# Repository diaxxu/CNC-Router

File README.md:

# CNC-Router

This is my homemade modular CNC machine, built from simple available parts. I designed everything in Fusion 360, researched every component, and chose them carefully. It’s not perfect, but it’s beautiful, and I genuinely enjoyed building it.

## Why I Made This

To get more hands on experience ? this is a very cool project. A CNC that can carve wood and maybe on a good day cut aluminum, isn't that great ?

## 3D Model 

### Front View

### Side View

### Full Assembly

## Schematics and PCB Layout
**made it in Kicad** 

(i re-routed this 5 or 6 times 😭) </br>

im really bad at soldering :c </br>
### Schematic ( wire diagram ) 

## Firmware Installation 
1- assemble your driver board ( put the driver in plane ) Insert it into the Arduino Uno header <br/>
2- connect the arduino uno your pc<br/> 
3- download grbl.zip from the github <br/>
4- upload the code <br/>
5- install Universal Gcode sender <br/>
6- learn CAM software or use Easel <br/>
7- enjoy the results <br/>

## BOM (Bill of Materials)

Here is the secret sauce!!

| Item                                     | Quantity | Unit |   link|
| ---------------------------------------- | -------- | ---- |      ---------------------------------------- |
| T8 Lead Screw 2mm lead 500 mm (with nut) | 1        | pcs  |          https://www.aliexpress.com/item/1005007457419235.html?spm=a2g0o.productlist.main.1.13e96abcm3Qxf8&algo_pvid=abe9b885-1ea4-4bde-81db-ef474f83f248&pdp_ext_f=%7B%22order%22%3A%221334%22%2C%22eval%22%3A%221%22%2C%22fromPage%22%3A%22search%22%7D&utparam-url=scene%3Asearch%7Cquery_from%3A%7Cx_object_id%3A1005007457419235%7C_p_origin_prod%3A                                      |
| T8 screw round                           | 10       | pcs  |  https://www.aliexpress.com/item/1005007438925484.html?spm=a2g0o.productlist.main.1.663d47d6Xk5GhJ&algo_pvid=a073f148-42f6-4d7e-ae10-4d699659c8fb&pdp_ext_f=%7B%22order%22%3A%22195%22%2C%22eval%22%3A%221%22%2C%22fromPage%22%3A%22search%22%7D&utparam-url=scene%3Asearch%7Cquery_from%3A%7Cx_object_id%3A1005007438925484%7C_p_origin_prod%3A                                         |
| LM6UU linear bearing                     | 4        | pcs  |  https://www.aliexpress.com/item/1005007791097936.html?spm=a2g0o.productlist.main.1.3edb5583NcR1Fg&algo_pvid=f794e0da-0bcf-4ead-a3f3-0a383e8e83e8&pdp_ext_f=%7B%22order%22%3A%221004%22%2C%22eval%22%3A%221%22%2C%22orig_sl_item_id%22%3A%221005007791097936%22%2C%22orig_item_id%22%3A%221005006822845504%22%2C%22fromPage%22%3A%22search%22%7D&utparam-url=scene%3Asearch%7Cquery_from%3A%7Cx_object_id%3A1005007791097936%7C_p_origin_prod%3A1005006822845504                                         |
| NEMA17 stepper motor                     | 3        | pcs  |       https://www.aliexpress.com/item/1005003874936862.html?spm=a2g0o.productlist.main.1.3135692aSn653o&algo_pvid=01a18a8a-84a6-4b73-875e-59fb750efacf&pdp_ext_f=%7B%22order%22%3A%222333%22%2C%22eval%22%3A%221%22%2C%22fromPage%22%3A%22search%22%7D&utparam-url=scene%3Asearch%7Cquery_from%3A%7Cx_object_id%3A1005003874936862%7C_p_origin_prod%3A                                     |
| M5 T-nut for 2020 extrusion              | 100      | pcs  |     https://www.aliexpress.com/item/1005007805744044.html?spm=a2g0o.productlist.main.1.21166df09vtnEI&algo_pvid=d509197c-5494-4b8d-bd75-dd62f6435446&pdp_ext_f=%7B%22order%22%3A%222654%22%2C%22spu_best_type%22%3A%22price%22%2C%22eval%22%3A%221%22%2C%22orig_sl_item_id%22%3A%221005007805744044%22%2C%22orig_item_id%22%3A%221005007342221792%22%2C%22fromPage%22%3A%22search%22%7D&utparam-url=scene%3Asearch%7Cquery_from%3A%7Cx_object_id%3A1005007805744044%7C_p_origin_prod%3A1005007342221792                                          |
| Shaft decoupler                          | 5        | pcs  |     https://www.aliexpress.com/item/1005006031199563.html?spm=a2g0o.productlist.main.9.44996081ngFjnD&algo_pvid=ea42cc85-9204-4080-b783-f4bf5ca40faf&pdp_ext_f=%7B%22order%22%3A%221177%22%2C%22eval%22%3A%221%22%2C%22fromPage%22%3A%22search%22%7D&utparam-url=scene%3Asearch%7Cquery_from%3A%7Cx_object_id%3A1005006031199563%7C_p_origin_prod%3A             |
| Limit switch (mechanical)                | 5        | pcs  |           https://www.aliexpress.com/item/1005010111182286.html?spm=a2g0o.productlist.main.1.3abbDG8vDG8vWA&algo_pvid=5933562e-580b-41ea-b598-2eb9fccb11d4&pdp_ext_f=%7B%22order%22%3A%223%22%2C%22eval%22%3A%221%22%2C%22fromPage%22%3A%22search%22%7D&utparam-url=scene%3Asearch%7Cquery_from%3A%7Cx_object_id%3A1005010111182286%7C_p_origin_prod%3A        |           
| Smooth shaft ~8mm x 500mm                | 2        | pcs  |               https://www.aliexpress.com/item/1005006104915821.html?spm=a2g0o.productlist.main.1.799f489bStEF77&algo_pvid=020c6d09-a195-4892-a017-91578b69bc51&pdp_ext_f=%7B%22order%22%3A%22162%22%2C%22eval%22%3A%221%22%2C%22fromPage%22%3A%22search%22%7D&utparam-url=scene%3Asearch%7Cquery_from%3A%7Cx_object_id%3A1005006104915821%7C_p_origin_prod%3A      |
| 2020 T-slot extrusion 300mm              | 4        | pcs  |                https://www.aliexpress.com/item/1005002652962344.html?spm=a2g0o.productlist.main.2.2e3437d7dGcIn6&algo_pvid=0aca7721-a8b6-4cf1-8678-ae9d48901605&pdp_ext_f=%7B%22order%22%3A%22609%22%2C%22eval%22%3A%221%22%2C%22fromPage%22%3A%22search%22%7D&utparam-url=scene%3Asearch%7Cquery_from%3A%7Cx_object_id%3A1005002652962344%7C_p_origin_prod%3A       |
| Emergency stop button                    | 1        | pcs  |            https://www.aliexpress.com/item/4000144892605.html?spm=a2g0o.productlist.main.6.33636377MQJT7H&algo_pvid=5d4f84aa-a965-43b3-a225-a805972d57df&pdp_ext_f=%7B%22order%22%3A%22186%22%2C%22eval%22%3A%221%22%2C%22fromPage%22%3A%22search%22%7D&utparam-url=scene%3Asearch%7Cquery_from%3A%7Cx_object_id%3A4000144892605%7C_p_origin_prod%3A         |
| Spindle                                  | 1        | pcs  |              https://www.aliexpress.com/item/1005006435477384.html?spm=a2g0o.productlist.main.9.2c031bb1jvPHgq&algo_pvid=c00a937d-d03c-4e7d-8a0f-f253cf034e65&pdp_ext_f=%7B%22order%22%3A%22110%22%2C%22eval%22%3A%221%22%2C%22fromPage%22%3A%22search%22%7D&utparam-url=scene%3Asearch%7Cquery_from%3A%7Cx_object_id%3A1005006435477384%7C_p_origin_prod%3A          |
| 4 flute HRC65 end mill                   | 4        | pcs  |                 https://www.aliexpress.com/item/1005006112116580.html?spm=a2g0o.productlist.main.1.28a91ef71Q6Qi6&algo_pvid=7d58d743-c4fb-4f96-9785-83c5d507e746&pdp_ext_f=%7B%22order%22%3A%223827%22%2C%22eval%22%3A%221%22%2C%22fromPage%22%3A%22search%22%7D&utparam-url=scene%3Asearch%7Cquery_from%3A%7Cx_object_id%3A1005006112116580%7C_p_origin_prod%3A          |
| Esp-32 wroom32                           |  1       | pcs  |          https://www.aliexpress.com/item/1005007117977294.html?spm=a2g0o.productlist.main.4.378a251bueFwB6&aem_p4p_detail=202512120410314090179256483500000207938&algo_pvid=bdf25448-9590-4bd6-97b4-afa84b8659dc&pdp_ext_f=%7B%22order%22%3A%22475%22%2C%22eval%22%3A%221%22%2C%22fromPage%22%3A%22search%22%7D&utparam-url=scene%3Asearch%7Cquery_from%3A%7Cx_object_id%3A1005007117977294%7C_p_origin_prod%3A&search_p4p_id=202512120410314090179256483500000207938_1              |
| Capacitor 100uF                 | 40        | pcs   |                           https://www.aliexpress.com/item/1005007792451411.html?spm=a2g0o.productlist.main.2.2ba17329lFhLJc&algo_pvid=0bc21b08-f505-443c-9b1e-3c51c8b5715e&pdp_ext_f=%7B%22order%22%3A%224566%22%2C%22eval%22%3A%221%22%2C%22orig_sl_item_id%22%3A%221005007792451411%22%2C%22orig_item_id%22%3A%221005009331775121%22%2C%22fromPage%22%3A%22search%22%7D&utparam-url=scene%3Asearch%7Cquery_from%3A%7Cx_object_id%3A1005007792451411%7C_p_origin_prod%3A1005009331775121            |
| DRV8825              |5      | pcs   |            https://www.aliexpress.com/item/1005006199405206.html?spm=a2g0o.productlist.main.1.2ac830b537vAT5&algo_pvid=251ba9a3-c089-40c5-95d6-3f10fed98294&pdp_ext_f=%7B%22order%22%3A%221189%22%2C%22eval%22%3A%221%22%2C%22fromPage%22%3A%22search%22%7D&utparam-url=scene%3Asearch%7Cquery_from%3A%7Cx_object_id%3A1005006199405206%7C_p_origin_prod%3A           |
| irlz44n            |10     | pcs   |                     https://www.aliexpress.com/item/32895956089.html?spm=a2g0o.productlist.main.3.585c7f81SrpjDa&algo_pvid=217b9e85-fb72-4510-a7c3-e3ecc2203bdb&pdp_ext_f=%7B%22order%22%3A%22330%22%2C%22eval%22%3A%221%22%2C%22fromPage%22%3A%22search%22%7D&utparam-url=scene%3Asearch%7Cquery_from%3A%7Cx_object_id%3A32895956089%7C_p_origin_prod%3A              |
| 1N5819          |50     | pcs   |                       https://www.aliexpress.com/item/1005001552094086.html?algo_pvid=6702d0a0-3a5b-4a89-a69c-304c6e60e806&pdp_ext_f=%7B%22order%22%3A%223075%22%2C%22eval%22%3A%221%22%2C%22fromPage%22%3A%22search%22%7D&utparam-url=scene%3Asearch%7Cquery_from%3A%7Cx_object_id%3A1005001552094086%7C_p_origin_prod%3A       |
| Screw terminal         |10     | pcs   |                     https://www.aliexpress.com/item/1005001677869988.html?spm=a2g0o.productlist.main.4.22797cf5vgQYyY&aem_p4p_detail=20251212041208392676109231120000190813&algo_pvid=ef3df8c8-928a-4232-a6dc-efeceac0b4f4&pdp_ext_f=%7B%22order%22%3A%222679%22%2C%22eval%22%3A%221%22%2C%22fromPage%22%3A%22search%22%7D&utparam-url=scene%3Asearch%7Cquery_from%3A%7Cx_object_id%3A1005001677869988%7C_p_origin_prod%3A&search_p4p_id=20251212041208392676109231120000190813_1             |
| Pin headers 1*40pin        |10     | pcs   |                     https://www.aliexpress.com/item/32980998451.html?spm=a2g0o.productlist.main.4.6ff54f9dFpS61i&aem_p4p_detail=202512120412263191470227330580000181648&algo_pvid=725f76e7-70a3-44bd-9da3-b267a7eabeb5&pdp_ext_f=%7B%22order%22%3A%22149%22%2C%22eval%22%3A%221%22%2C%22fromPage%22%3A%22search%22%7D&utparam-url=scene%3Asearch%7Cquery_from%3A%7Cx_object_id%3A32980998451%7C_p_origin_prod%3A&search_p4p_id=202512120412263191470227330580000181648_1               |
| PSU 24V 16A       |1    | pcs   |                    https://www.aliexpress.com/item/1005003962776196.html?spm=a2g0o.productlist.main.1.14347ac40PBlA3&algo_pvid=1247abea-e56f-4125-8b5c-04adc4c23b2b&pdp_ext_f=%7B%22order%22%3A%2211%22%2C%22eval%22%3A%221%22%2C%22fromPage%22%3A%22search%22%7D&utparam-url=scene%3Asearch%7Cquery_from%3A%7Cx_object_id%3A1005003962776196%7C_p_origin_prod%3A|
| pcb cost | 5 | pcs |  https://www.allpcb.com/cart?protype=2&upfileid=797791 |
| 3d printing cost | 456 | grams |  fusion estimation |
### Total 
- in Mad : 3.512 </br>
- in Dollar : 384.72

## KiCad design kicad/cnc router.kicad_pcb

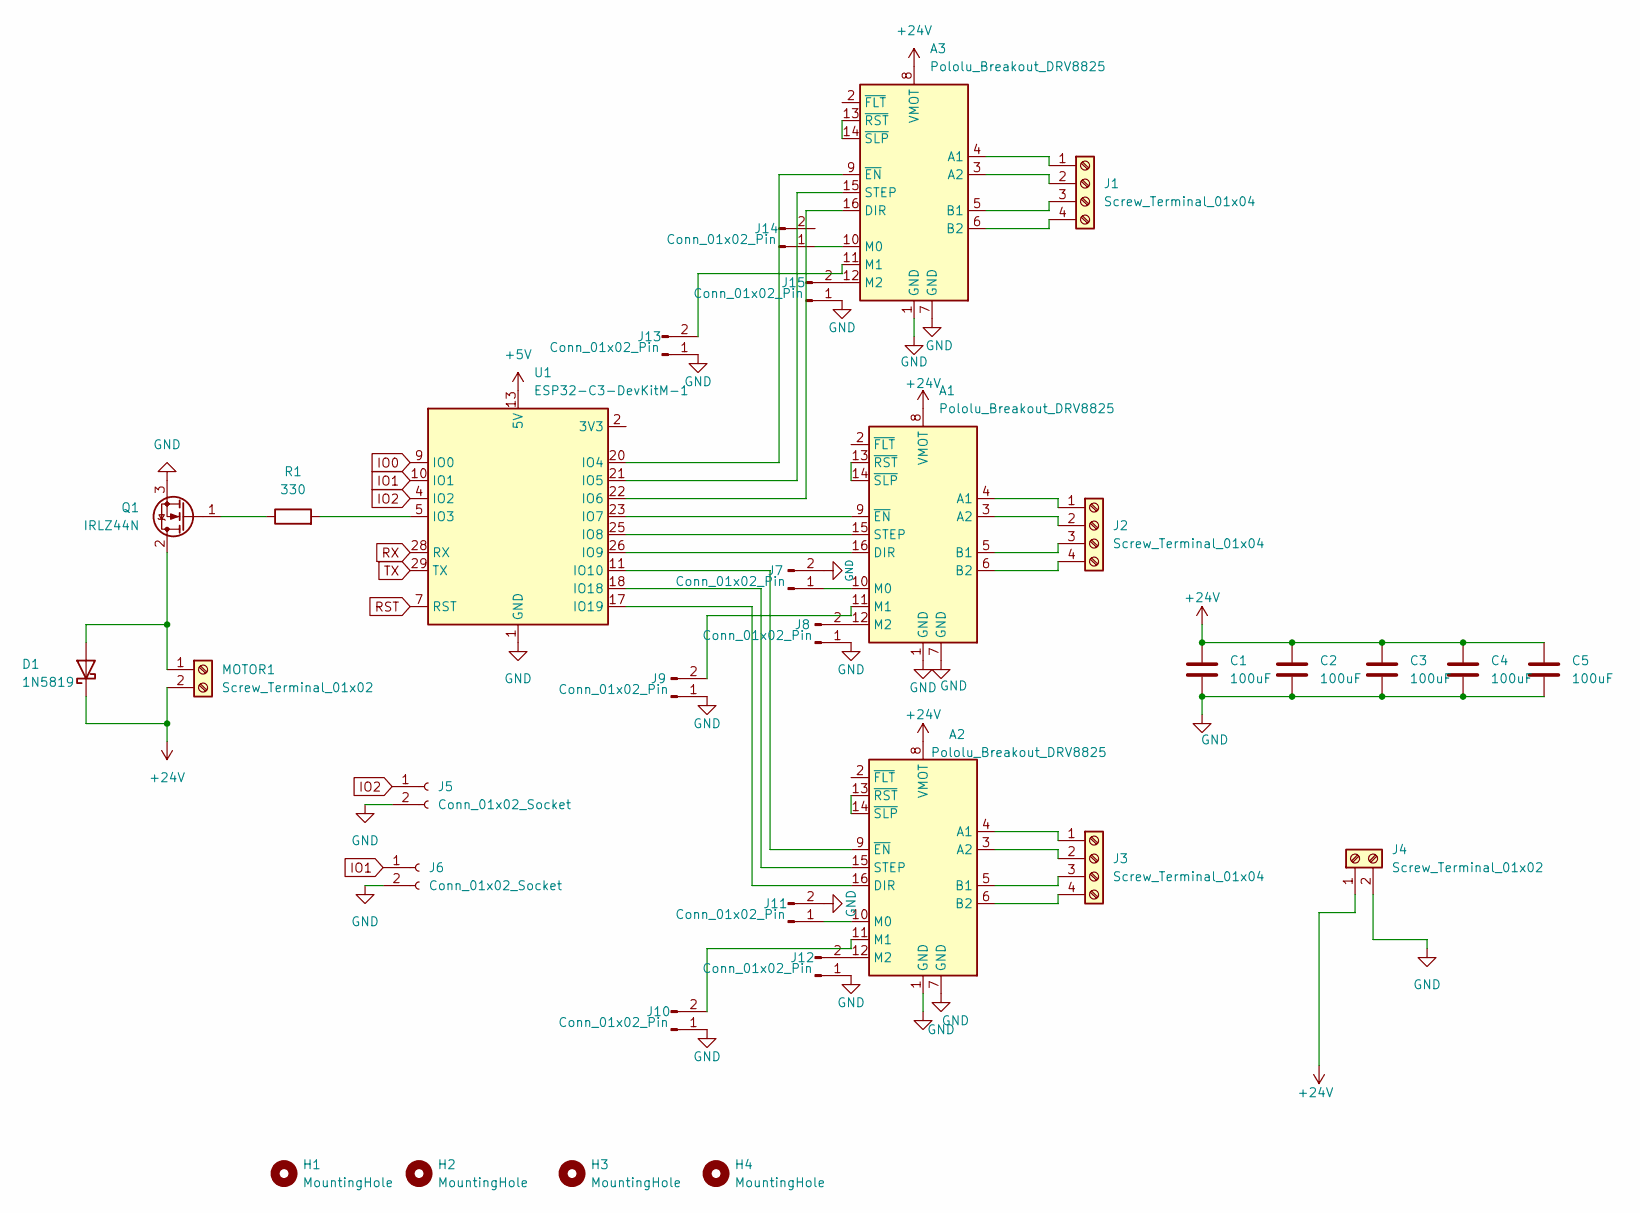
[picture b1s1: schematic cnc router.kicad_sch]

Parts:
A1, A2, A3: Pololu_Breakout_DRV8825; Pololu_Breakout-16_15.2x20.3mm
C1, C2, C3, C4, C5: 100uF; R_Axial_DIN0516_L15.5mm_D5.0mm_P30.48mm_Horizontal
D1: 1N5819; D_DO-41_SOD81_P10.16mm_Horizontal
H1, H2, H3, H4: MountingHole; MountingHole_2.1mm
J1, J2, J3: Screw_Terminal_01x04; TerminalBlock_Phoenix_MKDS-1,5-4-5.08_1x04_P5.08mm_Horizont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
J4: Screw_Terminal_01x02; TerminalBlock_Phoenix_MKDS-1,5-2_1x02_P5.00mm_Horizontal
J5, J6: Conn_01x02_Socket; PinSocket_1x02_P2.00mm_Vertical
J7, J8, J9, J10, J11, J12, J13, J14, J15: Conn_01x02_Pin; PinHeader_1x02_P2.54mm_Vertical
MOTOR1: Screw_Terminal_01x02; TerminalBlock_Phoenix_MKDS-1,5-2_1x02_P5.00mm_Horizontal
Q1: IRLZ44N; TO-220-3_Vertical
R1: 330; R_Axial_Power_L20.0mm_W6.4mm_P22.40mm
U1: ESP32-C3-DevKitM-1

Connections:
+5V: U1.13 (5V), U1.14 (5V)
+24V: A1.8 (VMOT), A2.8 (VMOT), A3.8 (VMOT), C1.1, C2.1, C3.1, C4.1, C5.1, D1.1 (K), J4.1, MOTOR1.2
GND: A1.1 (GND), A1.7 (GND), A2.1 (GND), A2.7 (GND), A3.1 (GND), A3.7 (GND), C1.2, C2.2, C3.2, C4.2, C5.2, J4.2, J5.2, J6.2, J7.2, J8.1, J9.1, J10.1, J11.2, J12.1, J13.1, J15.1, Q1.3 (S), U1.1 (GND), U1.6 (GND), U1.8 (GND), U1.12 (GND), U1.15 (GND), U1.16 (GND), U1.19 (GND), U1.24 (GND), U1.27 (GND), U1.30 (GND)
IO0: U1.9 (IO0)
IO1: J6.1, U1.10 (IO1)
IO2: J5.1, U1.4 (IO2)
unnamed: A1.4 (A1), J2.1
unnamed: A1.3 (A2), J2.2
unnamed: A1.5 (B1), J2.3
unnamed: A1.6 (B2), J2.4
unnamed: A1.16 (DIR), U1.26 (IO9)
unnamed: A1.10 (M0), J7.1
unnamed: A1.11 (M1), J9.2
unnamed: A1.12 (M2), J8.2
unnamed: A1.15 (STEP), U1.25 (IO8)
unnamed: A1.9 (~EN), U1.23 (IO7)
unnamed: A1.13 (~RST), A1.14 (~SLP)
unnamed: A2.4 (A1), J3.1
unnamed: A2.3 (A2), J3.2
unnamed: A2.5 (B1), J3.3
unnamed: A2.6 (B2), J3.4
unnamed: A2.16 (DIR), U1.17 (IO19)
unnamed: A2.10 (M0), J11.1
unnamed: A2.11 (M1), J10.2
unnamed: A2.12 (M2), J12.2
unnamed: A2.15 (STEP), U1.18 (IO18)
unnamed: A2.9 (~EN), U1.11 (IO10)
unnamed: A2.13 (~RST), A2.14 (~SLP)
unnamed: A3.4 (A1), J1.1
unnamed: A3.3 (A2), J1.2
unnamed: A3.5 (B1), J1.3
unnamed: A3.6 (B2), J1.4
unnamed: A3.16 (DIR), U1.22 (IO6)
unnamed: A3.10 (M0), J14.1
unnamed: A3.11 (M1), J13.2
unnamed: A3.12 (M2), J15.2
unnamed: A3.15 (STEP), U1.21 (IO5)
unnamed: A3.9 (~EN), U1.20 (IO4)
unnamed: A3.13 (~RST), A3.14 (~SLP)
unnamed: D1.2 (A), MOTOR1.1, Q1.2 (D)
unnamed: Q1.1 (G), R1.1
unnamed: U1.2 (3V3), U1.3 (3V3)
unnamed: R1.2, U1.5 (IO3)
RST: U1.7 (RST)
RX: U1.28 (RX)
TX: U1.29 (TX)

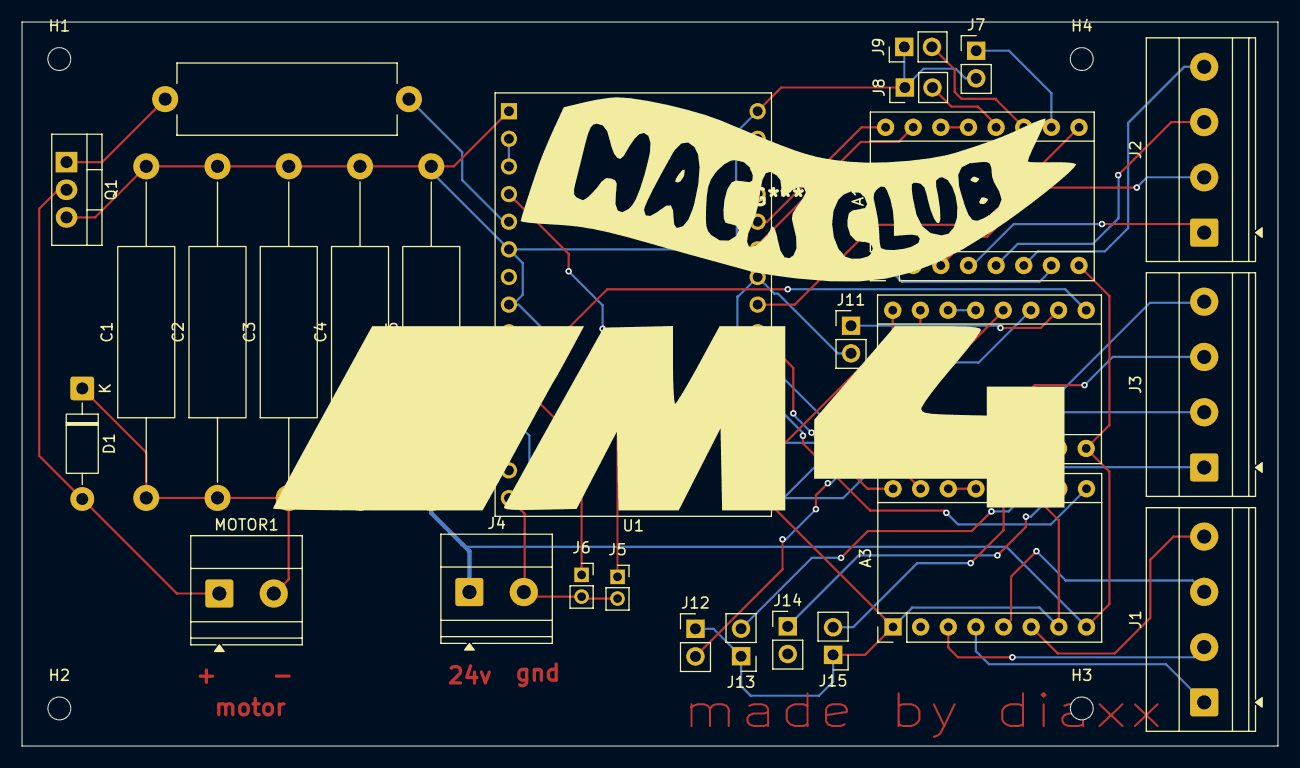
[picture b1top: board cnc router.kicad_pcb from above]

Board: 2 copper layers, 115.4 x 66.5 mm, 32 parts (0 on the bottom side), 42 nets.

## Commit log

2025-12-09 Update README to clarify BOM section
2025-12-10 Add old README for CNC Router project
    This README provides an overview of a homemade CNC router project, including its purpose, 3D models, wiring diagram, and a bill of materials.
2025-12-10 Replace 3D model images with new versions
    Updated image references for 3D model views in README.
2025-12-11 Add pricing details to BOM in README
    Updated BOM to include pricing in MAD and USD.
2025-12-11 Add pin mapping for SCDCNC ESP32 Shield
2025-12-11 Fix image paths and enhance schematic section
    Updated image paths and improved formatting for schematics.
2025-12-11 Rename a powersupply.step to PSU_case.step
2025-12-12 Add product links to BOM in README
    Added links to BOM items for easy access.
2025-12-29 Update README with PCB and 3D printing costs
    Added PCB and 3D printing cost details to the README.
2026-02-20 Revise README content and update images
    Updated images and text in the README for clarity and consistency.
2026-03-04 Update README with schematic and cost details
    Added schematic image and updated cost explanation.
2026-03-04 Add firmware installation section and update BOM
    Added firmware installation instructions and updated BOM with new items.
2026-03-04 Fix formatting in firmware installation instructions
2026-03-04 Fix spelling and enhance firmware installation steps
    Corrected spelling of 'aluminuim' to 'aluminum' and improved clarity in firmware installation instructions.
2026-03-10 Update README with CNC shield image and soldering note
    Added a CNC shield image and a note about soldering skills.
2026-03-10 Refactor README content and formatting
    Updated README with improved formatting and additional details.
